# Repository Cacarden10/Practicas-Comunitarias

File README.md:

# Practicas-Comunitarias
Repositorio con todos los archivos usados durante el desarrollo de las practicas comunitarias

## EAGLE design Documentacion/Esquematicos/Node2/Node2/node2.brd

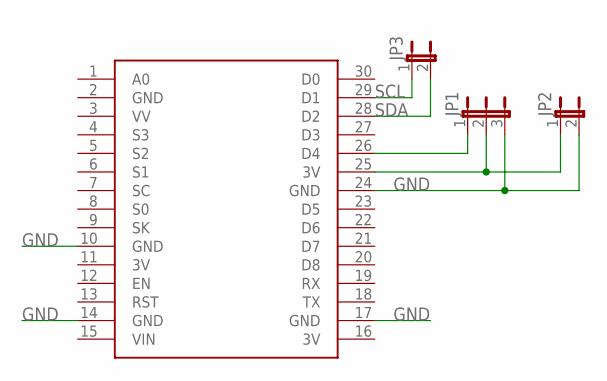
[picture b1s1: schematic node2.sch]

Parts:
JP1: JP2E; JP2
JP2, JP3: JP1E; JP1
U$1: NODEMCU

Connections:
3V: U$1.11 (3V), U$1.16 (3V)
GND: JP1.3, JP2.2, U$1.2 (GND), U$1.10 (GND), U$1.14 (GND), U$1.17 (GND), U$1.24 (GND)
unnamed: JP1.1, U$1.26 (D4)
unnamed: JP1.2, JP2.1, U$1.25 (3V)
SCL: JP3.1, U$1.29 (D1)
SDA: JP3.2, U$1.28 (D2)

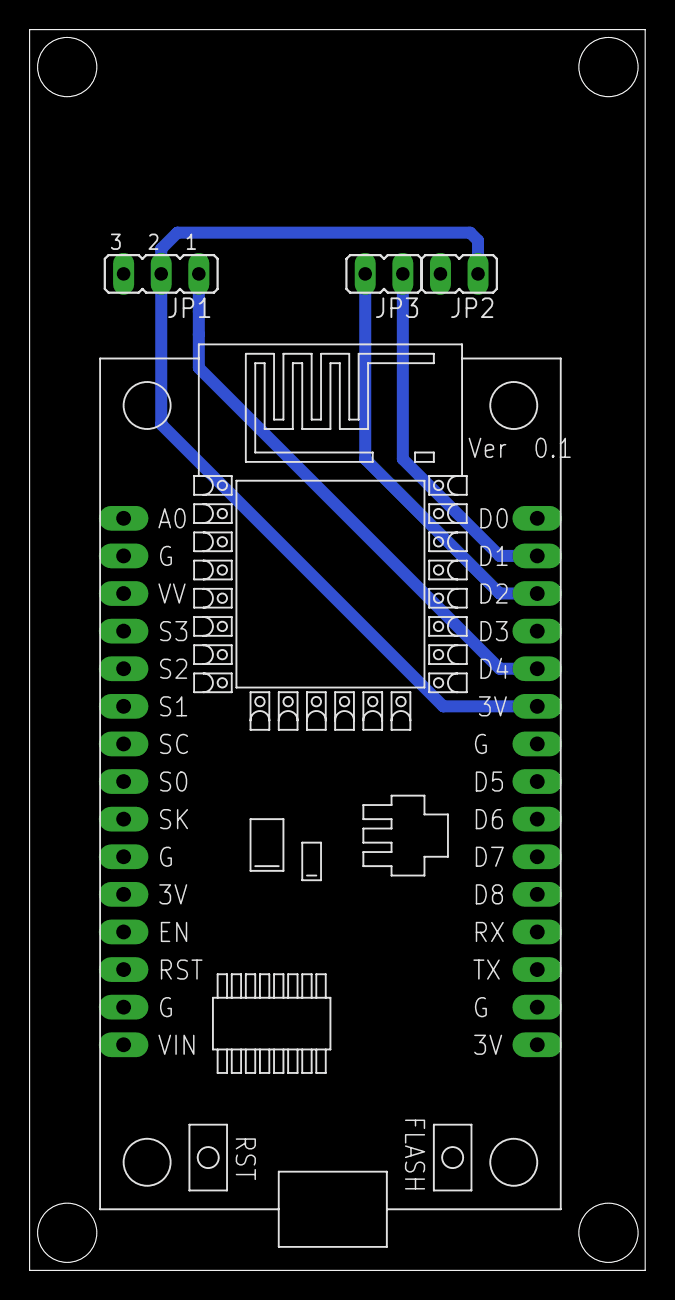
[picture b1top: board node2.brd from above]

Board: 2 copper layers, 41.6 x 83.8 mm, 4 parts (0 on the bottom side), 6 nets.

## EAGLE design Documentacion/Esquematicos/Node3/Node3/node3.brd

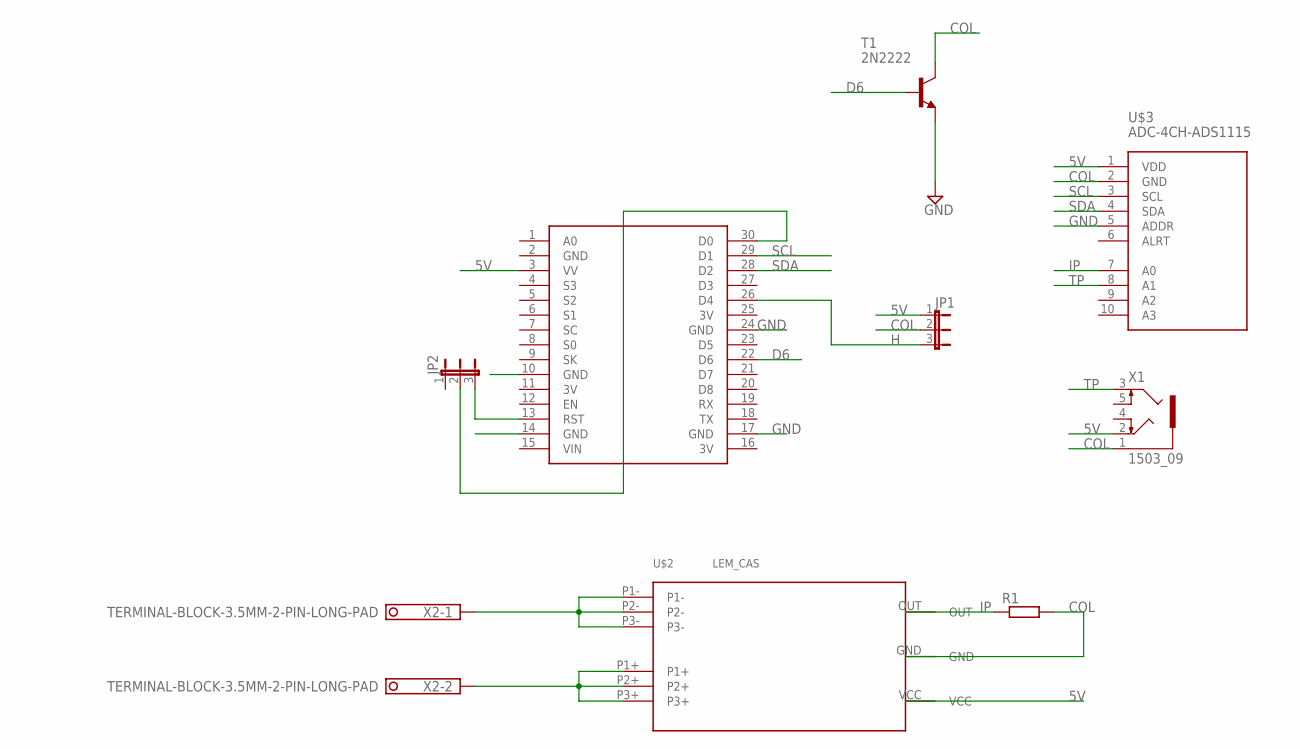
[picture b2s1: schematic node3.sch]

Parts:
JP1, JP2: JP2E; JP2
R1: R-EU_0207/10; 0207/10
T1: 2N2222; TO18
U$1: NODEMCU
U$2: LEM_CAS; LEMCAS
U$3: ADC-4CH-ADS1115
X1: 1503_09
X2: TERMINAL-BLOCK-3.5MM-2-PIN-LONG-PAD; TERMINAL-BLOCK-2-PIN-3.5MM-LONG-PAD

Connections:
3V: U$1.11 (3V), U$1.16 (3V), U$1.25 (3V)
5V: JP1.1, U$1.3 (VV), U$2.VCC, U$3.1 (VDD), X1.2
COL: JP1.2, R1.2, T1.3 (C), U$2.GND, U$3.2 (GND), X1.1
D6: T1.2 (B), U$1.22 (D6)
GND: T1.1 (E), U$1.2 (GND), U$1.10 (GND), U$1.14 (GND), U$1.17 (GND), U$1.24 (GND), U$3.5 (ADDR)
H: JP1.3, U$1.26 (D4)
IN: U$2.P1-, U$2.P2-, U$2.P3-, X2.1
IP: R1.1, U$2.OUT, U$3.7 (A0)
unnamed: JP2.3, U$1.13 (RST)
unnamed: JP2.2, U$1.30 (D0)
OUT: U$2.P1+, U$2.P2+, U$2.P3+, X2.2
SCL: U$1.29 (D1), U$3.3 (SCL)
SDA: U$1.28 (D2), U$3.4 (SDA)
TP: U$3.8 (A1), X1.3

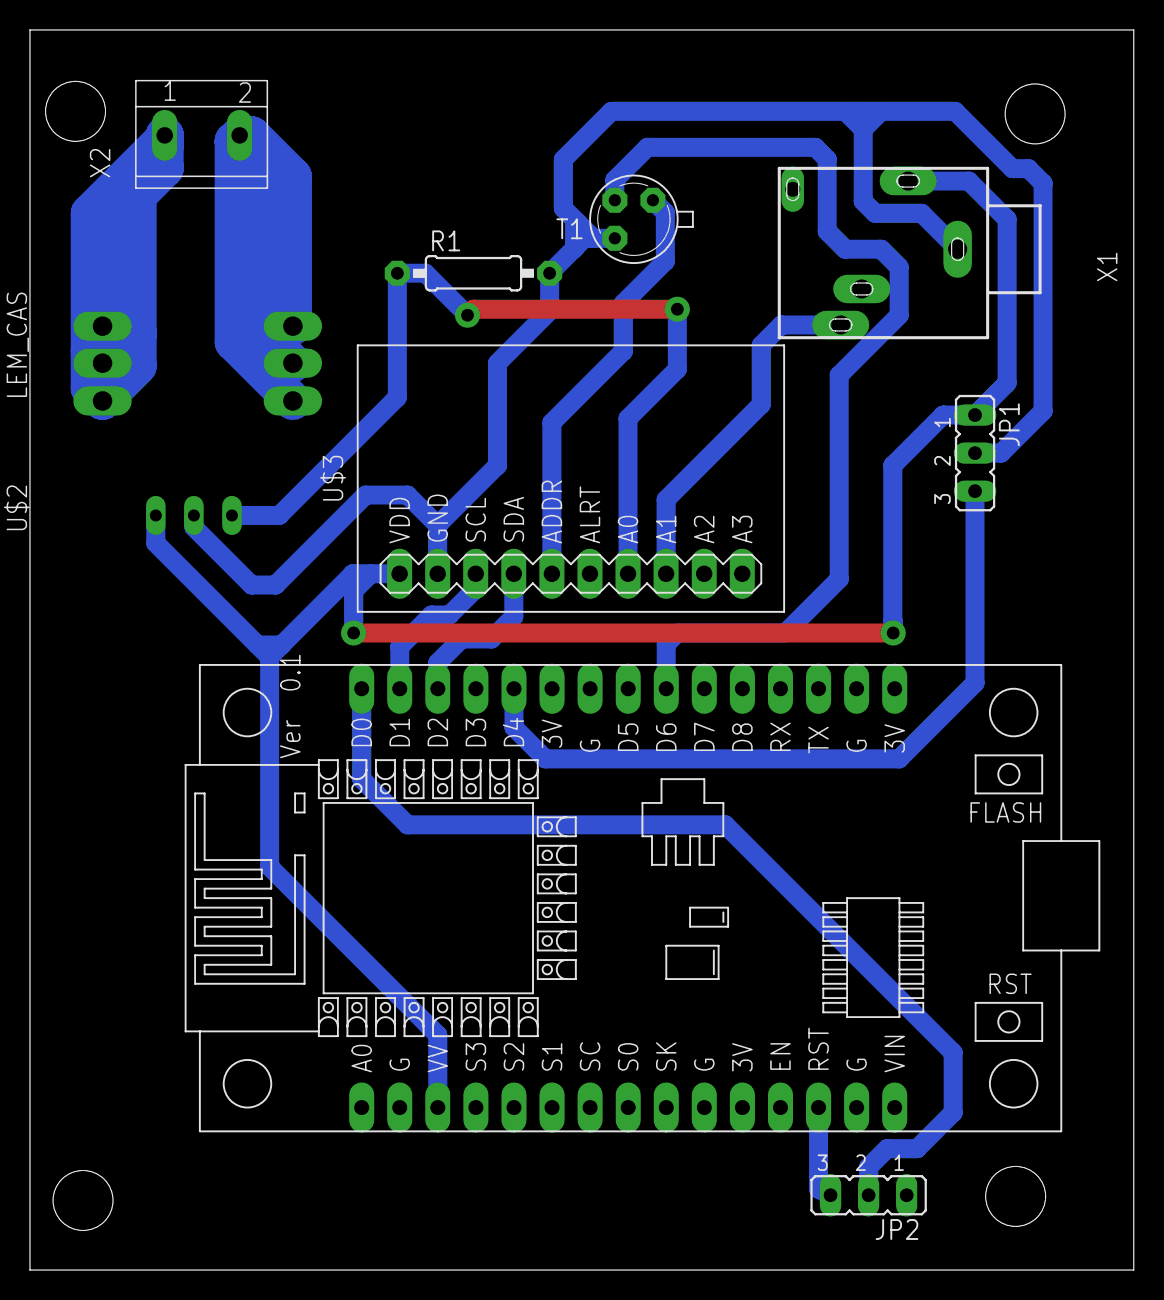
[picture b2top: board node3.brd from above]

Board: 2 copper layers, 73.6 x 82.7 mm, 9 parts (0 on the bottom side), 14 nets.

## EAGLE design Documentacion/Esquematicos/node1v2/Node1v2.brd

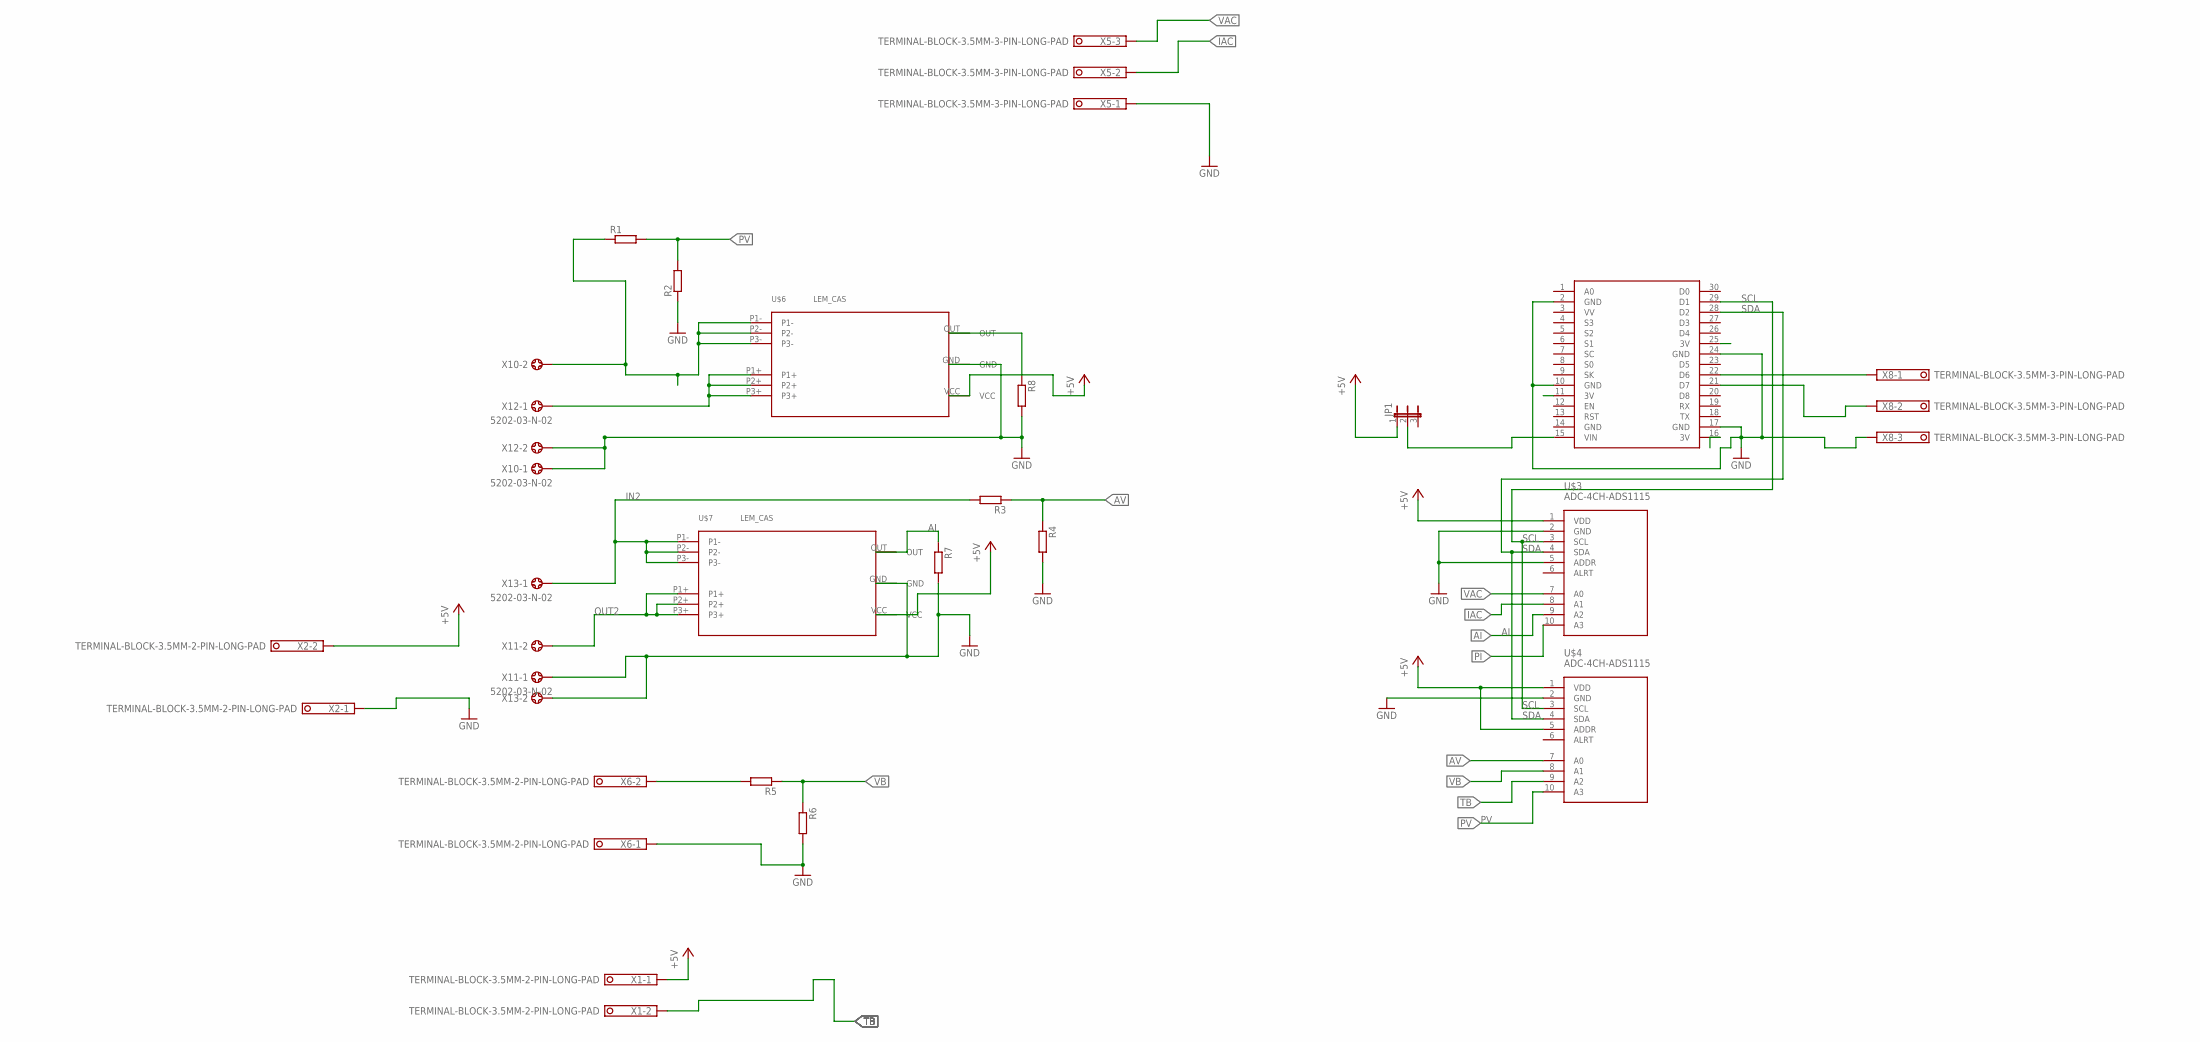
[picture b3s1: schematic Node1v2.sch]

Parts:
JP1: JP2E; JP2
R1, R2, R3, R4, R5, R6, R7, R8: R-EU_0207/12; 0207/12
U$3, U$4: ADC-4CH-ADS1115
U$5: NODEMCU
U$6, U$7: LEM_CAS; LEMCAS
X1, X2, X6: TERMINAL-BLOCK-3.5MM-2-PIN-LONG-PAD; TERMINAL-BLOCK-2-PIN-3.5MM-LONG-PAD
X5, X8: TERMINAL-BLOCK-3.5MM-3-PIN-LONG-PAD; TERMINAL-BLOCK-3-PIN-3.5MM-LONG-PAD
X10, X11, X12, X13: 5202-03-N-02

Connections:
+5V: JP1.1, U$3.1 (VDD), U$4.1 (VDD), U$4.5 (ADDR), U$6.VCC, U$7.VCC, X1.1, X2.2
AI: R7.1, U$3.9 (A2), U$7.OUT
AV: R3.1, R4.1, U$3.10 (A3)
GND: R2.1, R4.2, R6.2, R7.2, R8.2, U$3.2 (GND), U$3.5 (ADDR), U$4.2 (GND), U$5.2 (GND), U$5.10 (GND), U$5.14 (GND), U$5.17 (GND), U$5.24 (GND), U$6.GND, U$7.GND, X2.1, X5.1, X6.1, X8.3, X10.1, X11.1, X12.2, X13.2
IAC: U$3.8 (A1), X5.2
IN: R1.1, U$6.P1-, U$6.P2-, U$6.P3-, X10.2
IN2: R3.2, U$7.P1-, U$7.P2-, U$7.P3-, X13.1
unnamed: U$5.22 (D6), X8.1
unnamed: R5.2, X6.2
unnamed: U$5.21 (D7), X8.2
unnamed: JP1.2, U$5.15 (VIN)
OUT: U$6.P1+, U$6.P2+, U$6.P3+, X12.1
OUT2: U$7.P1+, U$7.P2+, U$7.P3+, X11.2
PI: R8.1, U$4.7 (A0), U$6.OUT
PV: R1.2, R2.2, U$4.10 (A3)
SCL: U$3.3 (SCL), U$4.3 (SCL), U$5.29 (D1)
SDA: U$3.4 (SDA), U$4.4 (SDA), U$5.28 (D2)
TB: U$4.9 (A2), X1.2
VAC: U$3.7 (A0), X5.3
VB: R5.1, R6.1, U$4.8 (A1)

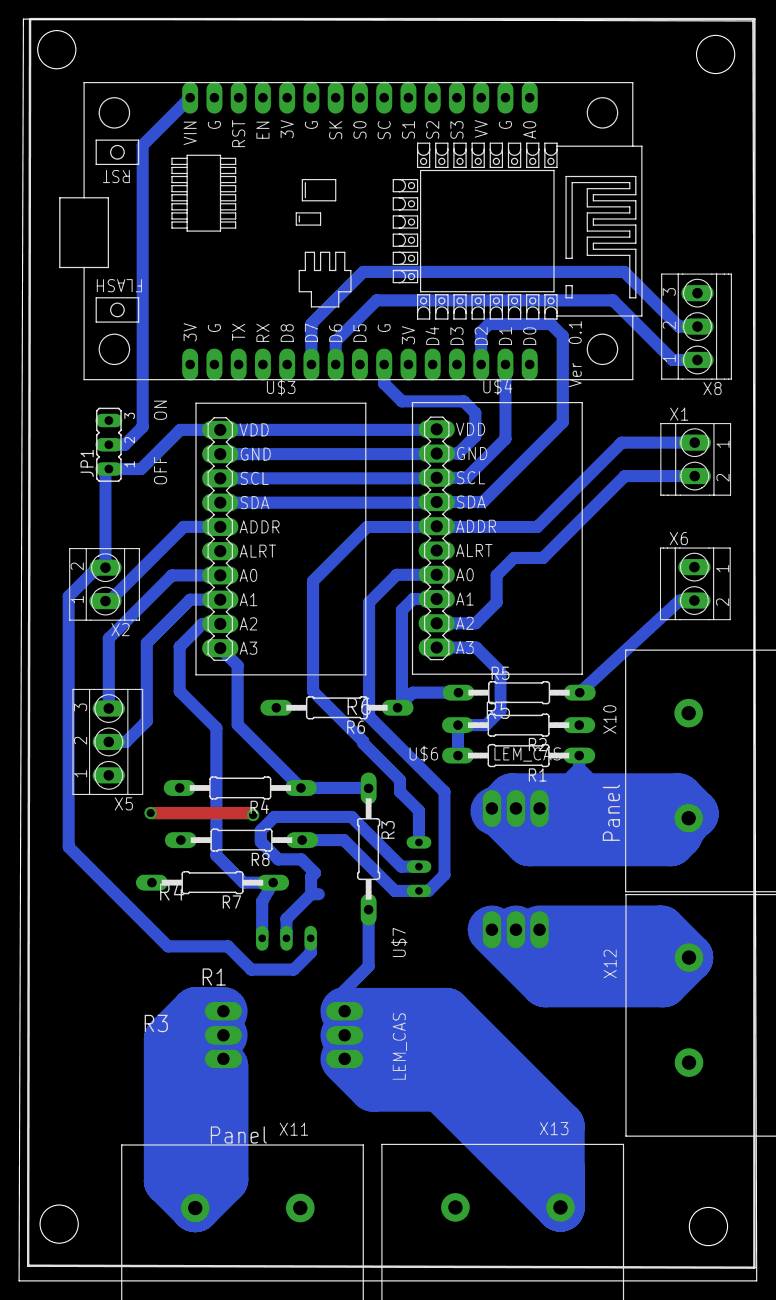
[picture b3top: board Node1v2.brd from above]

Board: 2 copper layers, 77.2 x 132.1 mm, 23 parts (0 on the bottom side), 20 nets.

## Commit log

2020-10-09 Documentacion
2020-10-09 Programacion

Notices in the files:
parts and their libraries:
diy-modules: Released under the Creative Commons Attribution 4.0 International License: http://creativecommons.org/licenses/by/4.0
